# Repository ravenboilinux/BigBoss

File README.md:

BigBoss
=======
First regulated box mode 

Goals
=====
1. selectable wattage in .1 steps up 100W
2. handles max 100W between the atty ranges .5 ohms to 2 ohms
3. uses 2 18650 batteries
4. charges the batteries by USB
5. has LCD display
6. LCD displays
  * selected wattage to the nearest .1 Wattage
  * battery power remaining
    - using a battery icon, with 4 section.
  * voltage coming out the DC-DC convert to the nearest .01 V
  * atty resistance to the nearest .1 Ohms
7. selected wattage is saved when there is no power to device
8. two button for wattage selection(up/down)
9. master button for turn off the device
10. fire button 
11. has reverse polority protection

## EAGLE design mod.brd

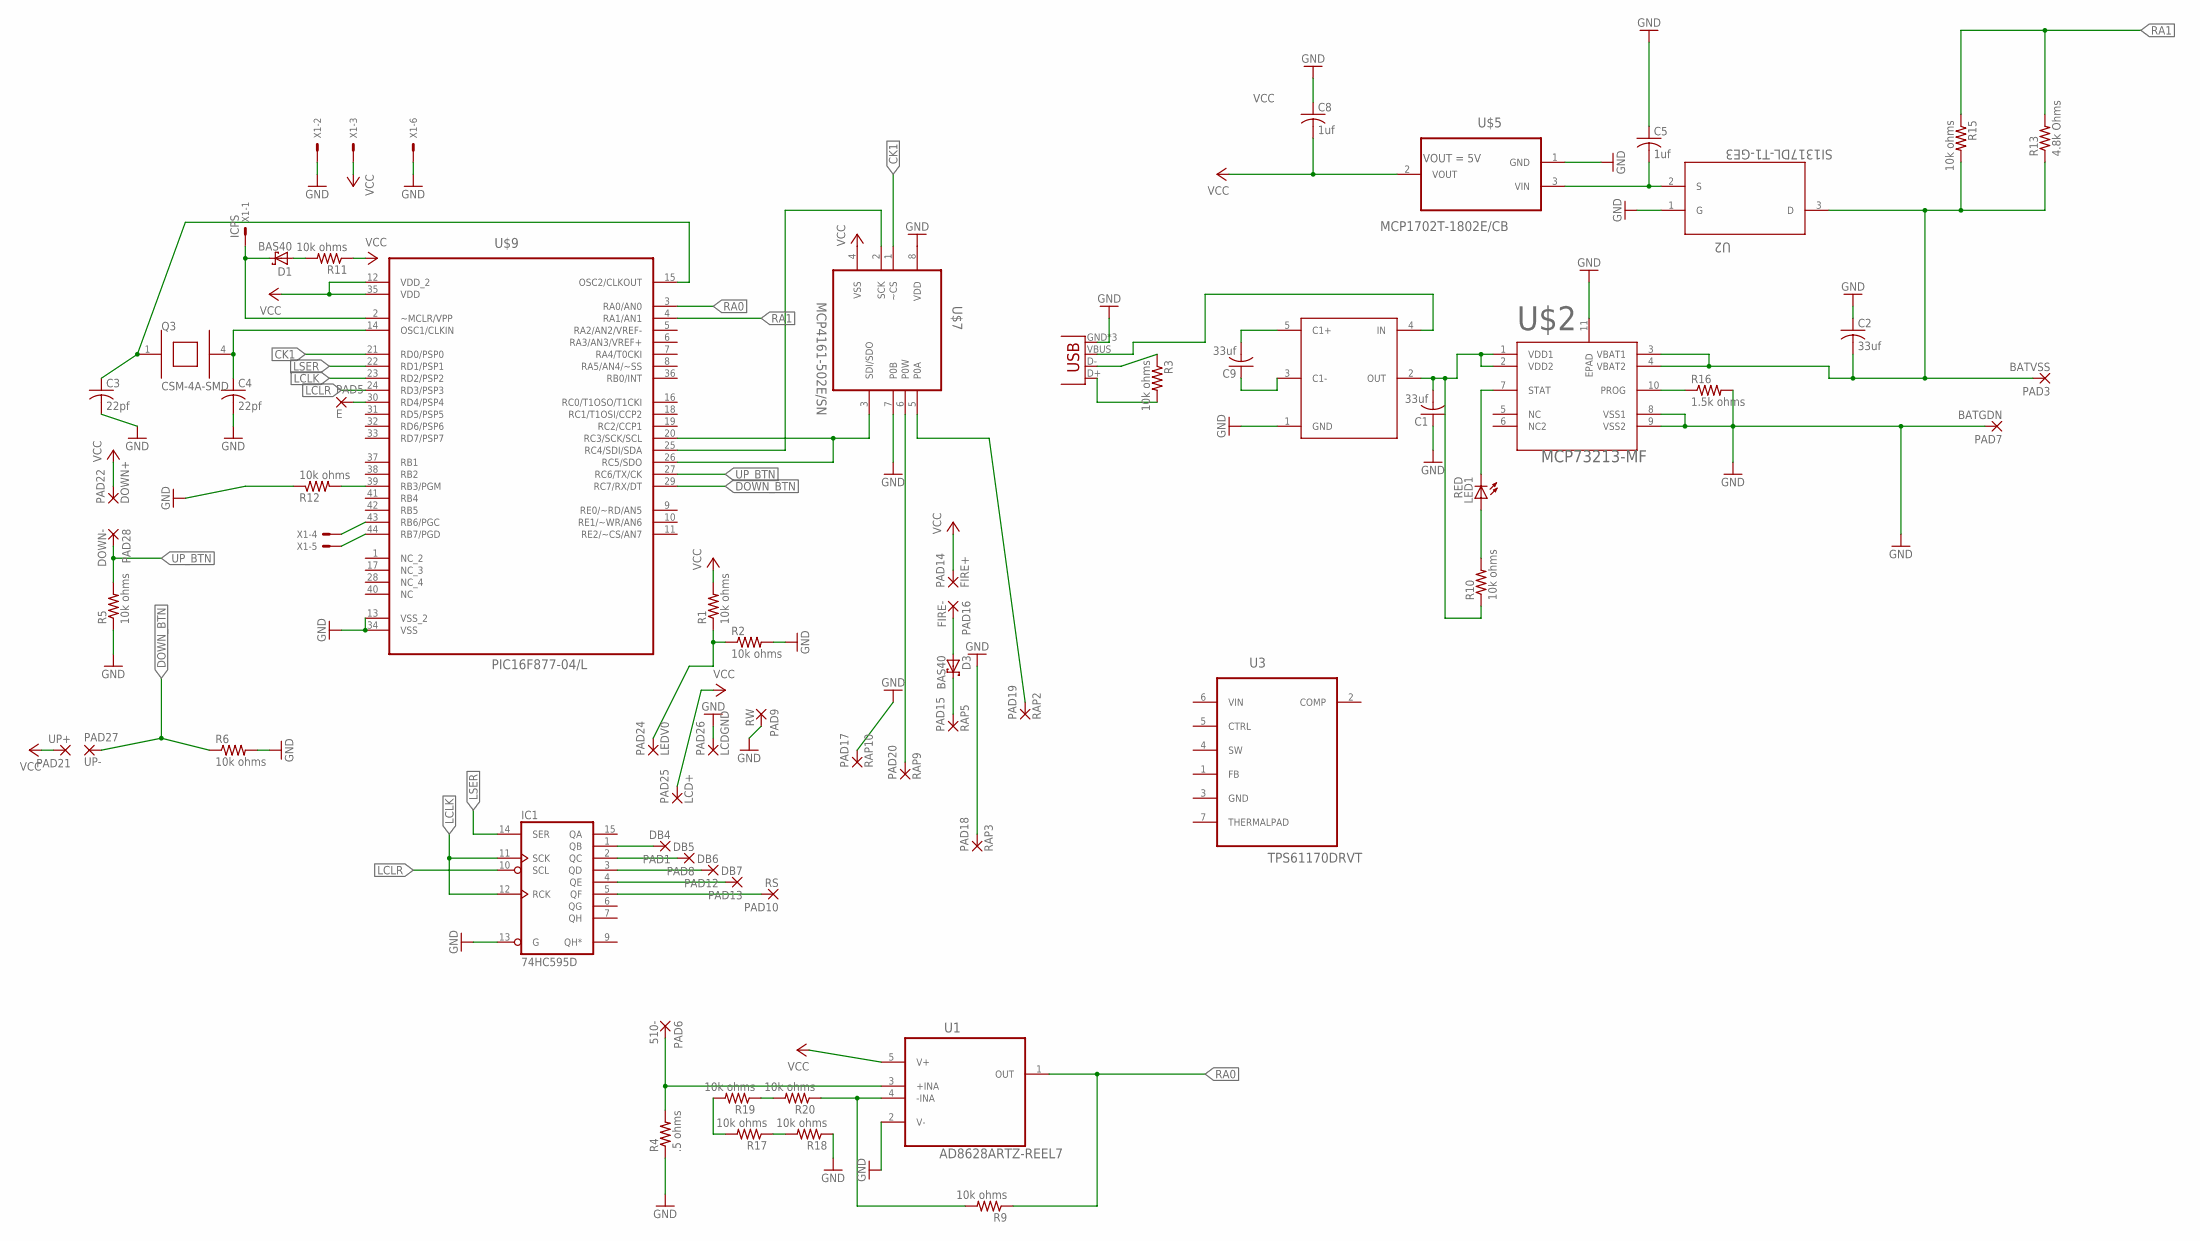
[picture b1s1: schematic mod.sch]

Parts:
C1, C2, C9: 33uf; C0805; MPN RC0805JR-1347KL
C3, C4: 22pf; C0805; MPN MC0805N220J501CT
C5, C8: 1uf; C0805; MPN RC0805JR-1347KL
D1, D3: BAS40; SOT23
IC1: 74HC595D; SO16
LED1: RED; CHIPLED_1206
PAD1: DB4; SMD1,27-2,54
PAD3: BATVSS; SMD1,27-2,54
PAD5: E; SMD1,27-2,54
PAD6: 510-; SMD1,27-2,54
PAD7: BATGDN; SMD1,27-2,54
PAD8: DB5; SMD1,27-2,54
PAD9: RW; SMD1,27-2,54
PAD10: RS; SMD1,27-2,54
PAD12: DB6; SMD1,27-2,54
PAD13: DB7; SMD1,27-2,54
PAD14: FIRE+; SMD1,27-2,54
PAD15: RAP5; SMD1,27-2,54
PAD16: FIRE-; SMD1,27-2,54
PAD17: RAP10; SMD1,27-2,54
PAD18: RAP3; SMD1,27-2,54
PAD19: RAP2; SMD1,27-2,54
PAD20: RAP9; SMD1,27-2,54
PAD21: UP+; SMD1,27-2,54
PAD22: DOWN+; SMD1,27-2,54
PAD24: LEDV0; SMD1,27-2,54
PAD25: LCD+; SMD1,27-2,54
PAD26: LCDGND; SMD1,27-2,54
PAD27: UP-; SMD1,27-2,54
PAD28: DOWN-; SMD1,27-2,54
Q3: CSM-4A-SMD; HC49/US
R1, R2, R5, R6, R9, R11, R12, R15, R17, R18, R19, R20: 10k ohms; R0805; MPN CRCW080510K0FKEB
R3, R10: 10k ohms; R0805; MPN CRCW0805220RJNEA
R4: .5 ohms; R0805; MPN CRCW080510K0FKEB
R13: 4.8k Ohms; R0805; MPN CRCW080510K0FKEB
R16: 1.5k ohms; R0805; MPN CRCW080510K0FKEB
U1: AD8628ARTZ-REEL7; SOT95P290X145-5N
U2: SI1317DL-T1-GE3; SOT65P210X110-3N
U3: TPS61170DRVT; SON65P210X210X80-7N
U$2: MCP73213-MF; 10-DFN
U$3: MAX1683-5-SOT23; SOT23-1
U$5: MCP1702T-1802E/CB; SOT95P300X145-3N
U$7: MCP4161-502E/SN; SOIC127P600X175-8N
U$9: PIC16F877-04/L; PLCC127P1752X1752X457-44N
X1: ICPS; 22-23-2061
X2: USB-MICROB

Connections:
AD_DC: C2.2, PAD3.1, R13.1, R15.2, U2.3 (D), U$2.3 (VBAT1), U$2.4 (VBAT2)
CK1: U$7.1 (~CS), U$9.21 (RD0/PSP0)
CLKOUT: C3.1, Q3.1, U$9.15 (OSC2/CLKOUT)
DOWN_BTN: PAD27.1, R6.1, U$9.29 (RC7/RX/DT)
GND: C1.1, C2.1, C3.2, C4.2, C5.1, C8.1, IC1.8 (GND), IC1.13 (G), PAD7.1, PAD9.1, PAD17.1, PAD18.1, PAD26.1, R2.2, R4.1, R5.1, R6.2, R12.1, R16.2, R18.1, U1.2 (V-), U2.1 (G), U$2.8 (VSS1), U$2.9 (VSS2), U$2.11 (EPAD), U$3.1 (GND), U$5.1 (GND), U$7.7 (P0B), U$7.8 (VDD), U$9.13 (VSS_2), U$9.34 (VSS), X1.2, X1.6, X2.GND, X2.MT1 (GND), X2.MT2 (GND)
LCLK: IC1.11 (SCK), IC1.12 (RCK), U$9.23 (RD2/PSP2)
LCLR: IC1.10 (SCL), U$9.24 (RD3/PSP3)
LSER: IC1.14 (SER), U$9.22 (RD1/PSP1)
unnamed: C5.2, U2.2 (S), U$5.3 (VIN)
unnamed: D3.1 (A), PAD16.1
unnamed: C4.1, Q3.4 (2), U$9.14 (OSC1/CLKIN)
unnamed: D3.3 (C), PAD15.1
unnamed: R3.1, X2.D-
unnamed: PAD20.1, U$7.6 (P0W)
unnamed: PAD19.1, U$7.5 (P0A)
unnamed: R3.2, X2.D+
unnamed: PAD6.1, R4.2, U1.3 (+INA)
unnamed: C9.2, U$3.5 (C1+)
unnamed: U$7.2 (SCK), U$9.25 (RC4/SDI/SDA)
unnamed: U$7.3 (SDI/SDO), U$9.20 (RC3/SCK/SCL), U$9.26 (RC5/SDO)
unnamed: R9.2, R20.1, U1.4 (-INA)
unnamed: IC1.1 (QB), PAD1.1
unnamed: D1.1 (A), R11.2
unnamed: D1.3 (C), U$9.2 (~MCLR/VPP), X1.1
unnamed: IC1.2 (QC), PAD8.1
unnamed: U$9.43 (RB6/PGC), X1.4
unnamed: U$9.44 (RB7/PGD), X1.5
unnamed: IC1.3 (QD), PAD12.1
unnamed: R12.2, U$9.39 (RB3/PGM)
unnamed: IC1.4 (QE), PAD13.1
unnamed: IC1.5 (QF), PAD10.1
unnamed: PAD5.1, U$9.30 (RD4/PSP4)
unnamed: U$3.4 (IN), X2.VBUS
unnamed: C9.1, U$3.3 (C1-)
unnamed: C1.2, R10.1, U$2.1 (VDD1), U$2.2 (VDD2), U$3.2 (OUT)
unnamed: LED1.A, R10.2
unnamed: LED1.C, U$2.7 (STAT)
unnamed: R16.1, U$2.10 (PROG)
unnamed: R19.1, R20.2
unnamed: R17.2, R19.2
unnamed: R17.1, R18.2
RA0: R9.1, U1.1 (OUT), U$9.3 (RA0/AN0)
RA1: R13.2, R15.1, U$9.4 (RA1/AN1)
UP_BTN: PAD28.1, R5.2, U$9.27 (RC6/TX/CK)
VCC: C8.2, IC1.16 (VCC), PAD14.1, PAD21.1, PAD22.1, PAD25.1, R1.2, R11.1, U1.5 (V+), U$5.2 (VOUT), U$7.4 (VSS), U$9.12 (VDD_2), U$9.35 (VDD), X1.3
VIN: U3.6 (VIN)
VO: PAD24.1, R1.1, R2.1

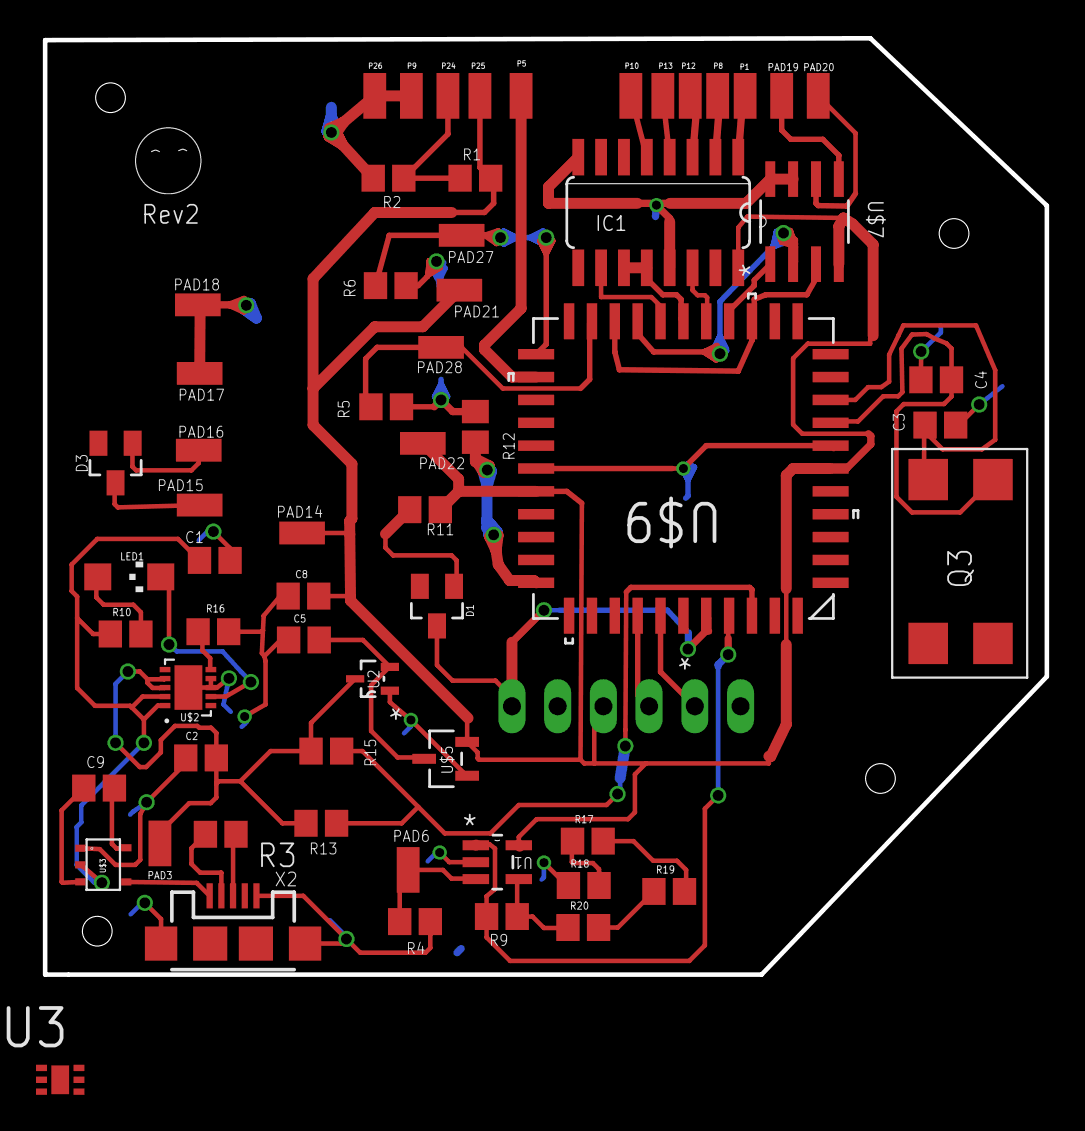
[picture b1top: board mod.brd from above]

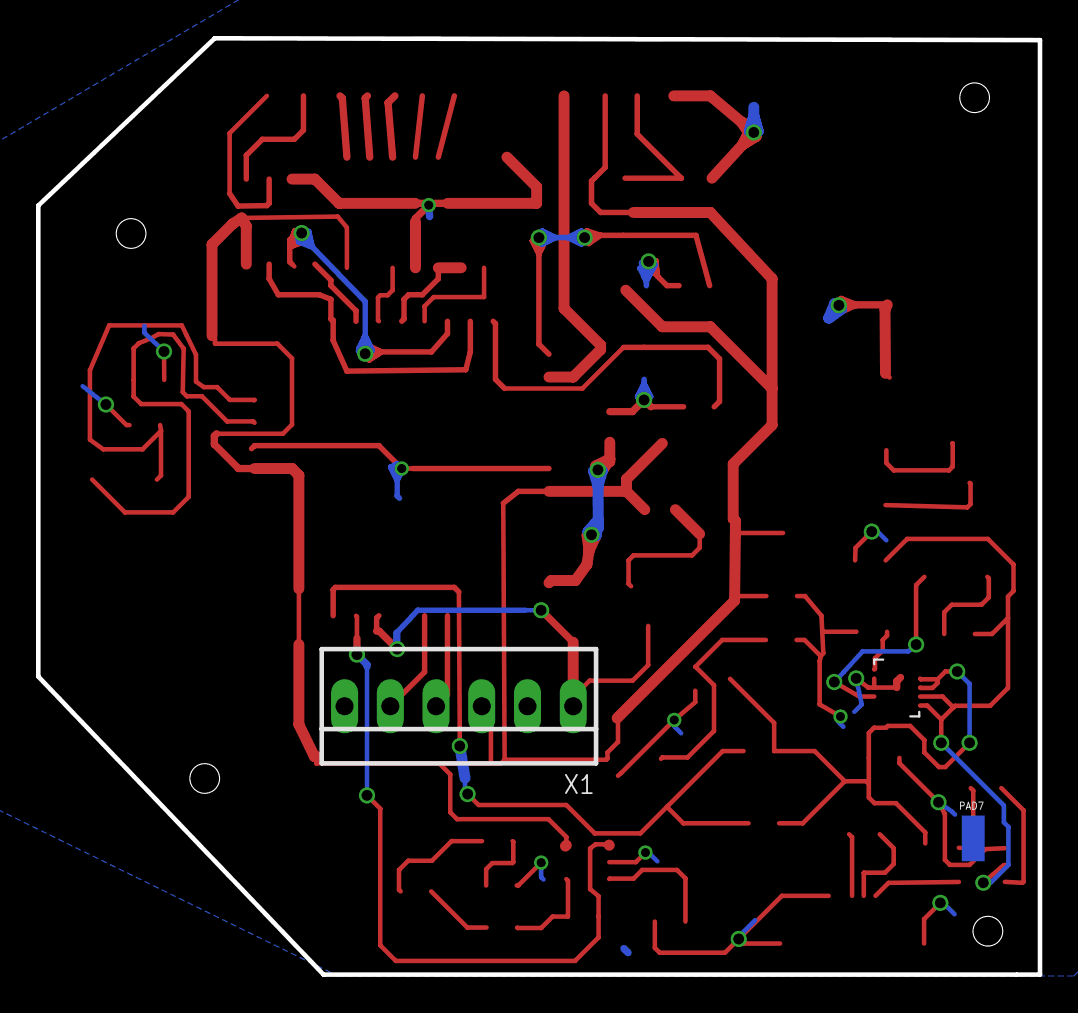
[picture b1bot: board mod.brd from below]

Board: 2 copper layers, 55.7 x 52.0 mm, 64 parts (2 on the bottom side), 46 nets.

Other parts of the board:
U$1: WINKLOGO

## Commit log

2014-11-05 gettting ignore completed
2014-11-05 Eagle Project
2014-11-13 datasheets for ICs
    using the MAX15046-MAX15046B-220655 buck converter
    datasheet for ICs
    Pic MCU Datasheets
    datasheet
2014-11-13 Product Docs

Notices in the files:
parts and their libraries:
SparkFun-Connectors: Licensing: Creative Commons ShareAlike 4.0 International - https://creativecommons.org/licenses/by-sa/4.0
